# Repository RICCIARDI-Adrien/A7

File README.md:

# A7

A hand-made computer based on a 8-bit PIC18F26K22 microcontroller.

## Specifications

### CPU

* 64MHz PIC18 core (up to 16MIPS).
* 3896 RAM bytes.
* 32768 16-bit instruction words.

### Display

* 128x64 STN display with white pixels on blue backlight.
* 8-bit data interface with the microcontroller.

### Input

* Standard PS/2 keyboard support.
* Connect via standard PS/2 6-pin mini DIN connector.

### External storage

* On-board 128KB EEPROM (256-byte pages, 6ms maximum to write a page).
* Connected to a fast 4MHz SPI bus (less than 600us to read a full 256-byte page).

### Communication

* Standard RS-232 DB9 connector.
* Communication settings : 115200 bauds, no parity, one stop bit.

### Power supply

* Standard power supply jack.
* Input voltage from 7V to 24V with at least 200mA.
* Polarity reversal protection.

# Hardware

Schematics and PCB have been made with Eagle 7.5.  

# Software

Use Microchip XC8 compiler to build software.  
You have to add the following environment variable for the build system to find the compiler-provided include files :
```
XC8_INCLUDES_PATH
```
The variable content must be the full path to the XC8 include directory. Below is an example for a Windows machine (don't forget to add quotation marks if the path contains spaces) :
```
"C:\Program Files\Microchip\xc8\v1.42\include"
```
  
In order to download applications on the A7, you have to set the following environment variable with the serial port device used to communicate with the A7 (like /dev/ttyS0, /dev/ttyUSB0...) :
```
A7_APPLICATION_DOWNLOAD_SERIAL_PORT_DEVICE
```

# Casing

Casing panels have been drawn with LibreCAD.

# Photo gallery

## 128x64 pixels graphical display

## Casing assembly

## Other viewing angles

## Booted operating system

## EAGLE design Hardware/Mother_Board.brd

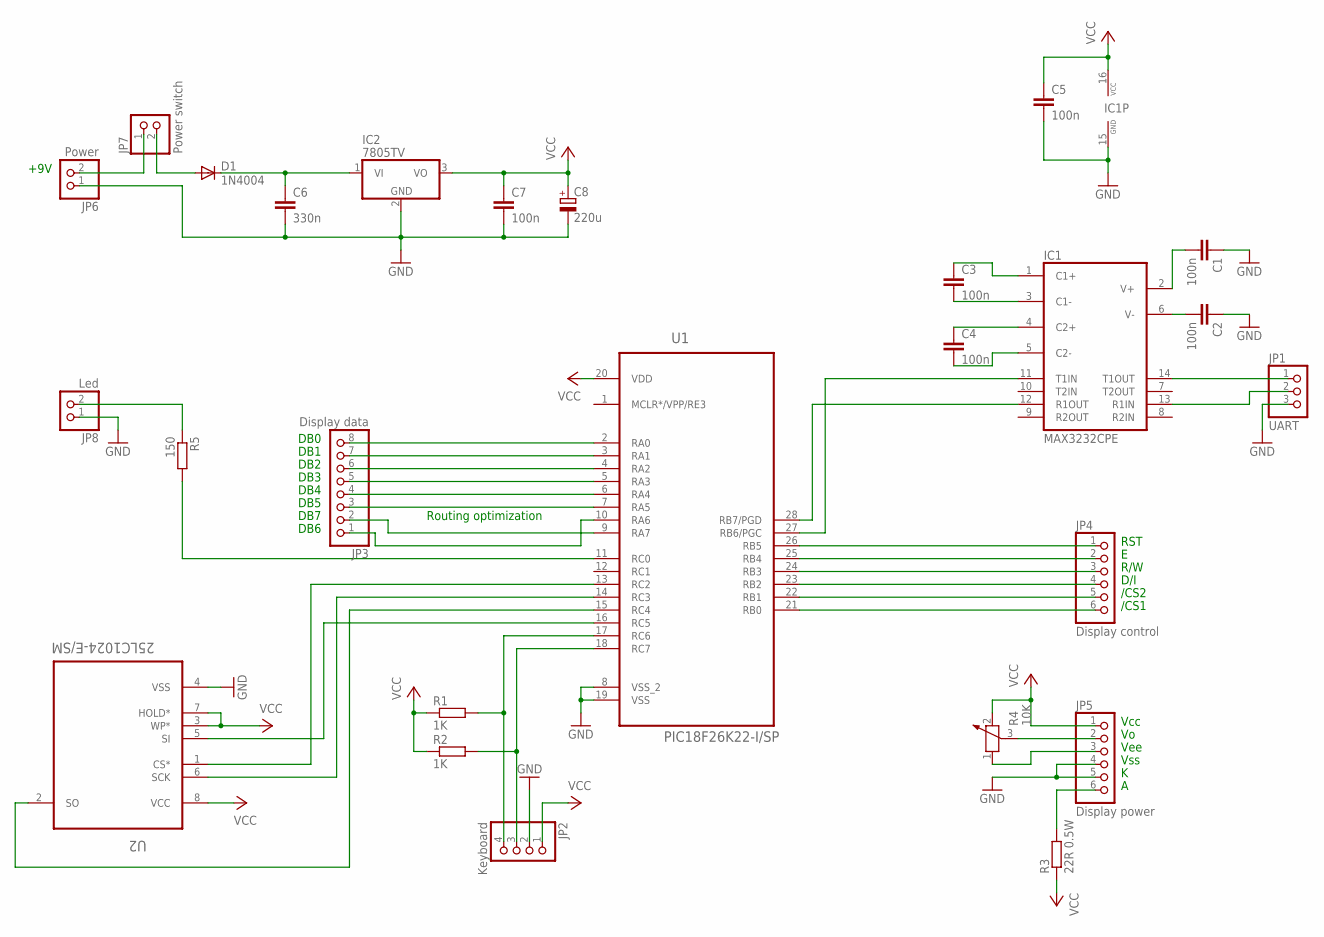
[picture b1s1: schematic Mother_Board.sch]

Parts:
C1, C2, C3, C4, C5, C7: 100n; C025-030X050
C6: 330n; C025-050X050
C8: 220u; B45181A
D1: 1N4004; DO41-10
IC1: MAX3232CPE; DIL16
IC2: 7805TV; TO220V
JP1: UART; 1X03
JP2: Keyboard; 1X04
JP3: Display data; 1X08
JP4: Display control; 1X06
JP5: Display power; 1X06
JP6: Power; 1X02
JP7: Power switch; 1X02
JP8: Led; 1X02
R1, R2: 1K; 0207/10
R3: 22R 0.5W; 0207/10
R4: 10K; PT-10S
R5: 150; 0207/10
U1: PIC18F26K22-I/SP; DIP254P762X508-28P
U2: 25LC1024-E/SM; SOIC127P794X203-8N

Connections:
GND: C1.1, C2.1, C5.2, C6.2, C7.2, C8.-, IC1.15 (GND), IC2.2 (GND), JP1.3, JP2.2, JP5.4, JP5.5, JP6.1, JP8.1, U1.8 (VSS_2), U1.19 (VSS), U2.4 (VSS)
unnamed: C3.1, IC1.1 (C1+)
unnamed: C3.2, IC1.3 (C1-)
unnamed: C4.1, IC1.4 (C2+)
unnamed: C4.2, IC1.5 (C2-)
unnamed: C1.2, IC1.2 (V+)
unnamed: IC1.12 (R1OUT), U1.28 (RB7/PGD)
unnamed: C2.2, IC1.6 (V-)
unnamed: IC1.11 (T1IN), U1.27 (RB6/PGC)
unnamed: IC1.14 (T1OUT), JP1.1
unnamed: IC1.13 (R1IN), JP1.2
unnamed: JP3.8, U1.2 (RA0)
unnamed: JP3.7, U1.3 (RA1)
unnamed: JP2.3, R2.2, U1.18 (RC7)
unnamed: JP2.4, R1.2, U1.17 (RC6)
unnamed: JP3.6, U1.4 (RA2)
unnamed: JP3.5, U1.5 (RA3)
unnamed: JP3.4, U1.6 (RA4)
unnamed: JP3.3, U1.7 (RA5)
unnamed: JP3.2, U1.9 (RA7)
unnamed: JP3.1, U1.10 (RA6)
unnamed: U1.16 (RC5), U2.5 (SI)
unnamed: U1.14 (RC3), U2.6 (SCK)
unnamed: U1.15 (RC4), U2.2 (SO)
unnamed: U1.13 (RC2), U2.1 (CS*)
unnamed: JP5.3, R4.1
unnamed: JP4.1, U1.26 (RB5)
unnamed: JP4.2, U1.25 (RB4)
unnamed: JP4.3, U1.24 (RB3)
unnamed: JP4.4, U1.23 (RB2)
unnamed: JP4.5, U1.22 (RB1)
unnamed: JP4.6, U1.21 (RB0)
unnamed: JP5.2, R4.3
unnamed: JP5.6, R3.2
unnamed: JP6.2, JP7.1
unnamed: D1.A, JP7.2
unnamed: C6.1, D1.C, IC2.1 (VI)
unnamed: R5.2, U1.11 (RC0)
unnamed: JP8.2, R5.1
VCC: C5.1, C7.1, C8.+, IC1.16 (VCC), IC2.3 (VO), JP2.1, JP5.1, R1.1, R2.1, R3.1, R4.2, U1.20 (VDD), U2.3 (WP*), U2.7 (HOLD*), U2.8 (VCC)

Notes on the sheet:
DB0
DB1
DB2
DB3
DB4
DB5
DB6
DB7
Vcc
Vee
Vss
/CS1
/CS2
D/I
R/W
RST
+9V
Routing optimization

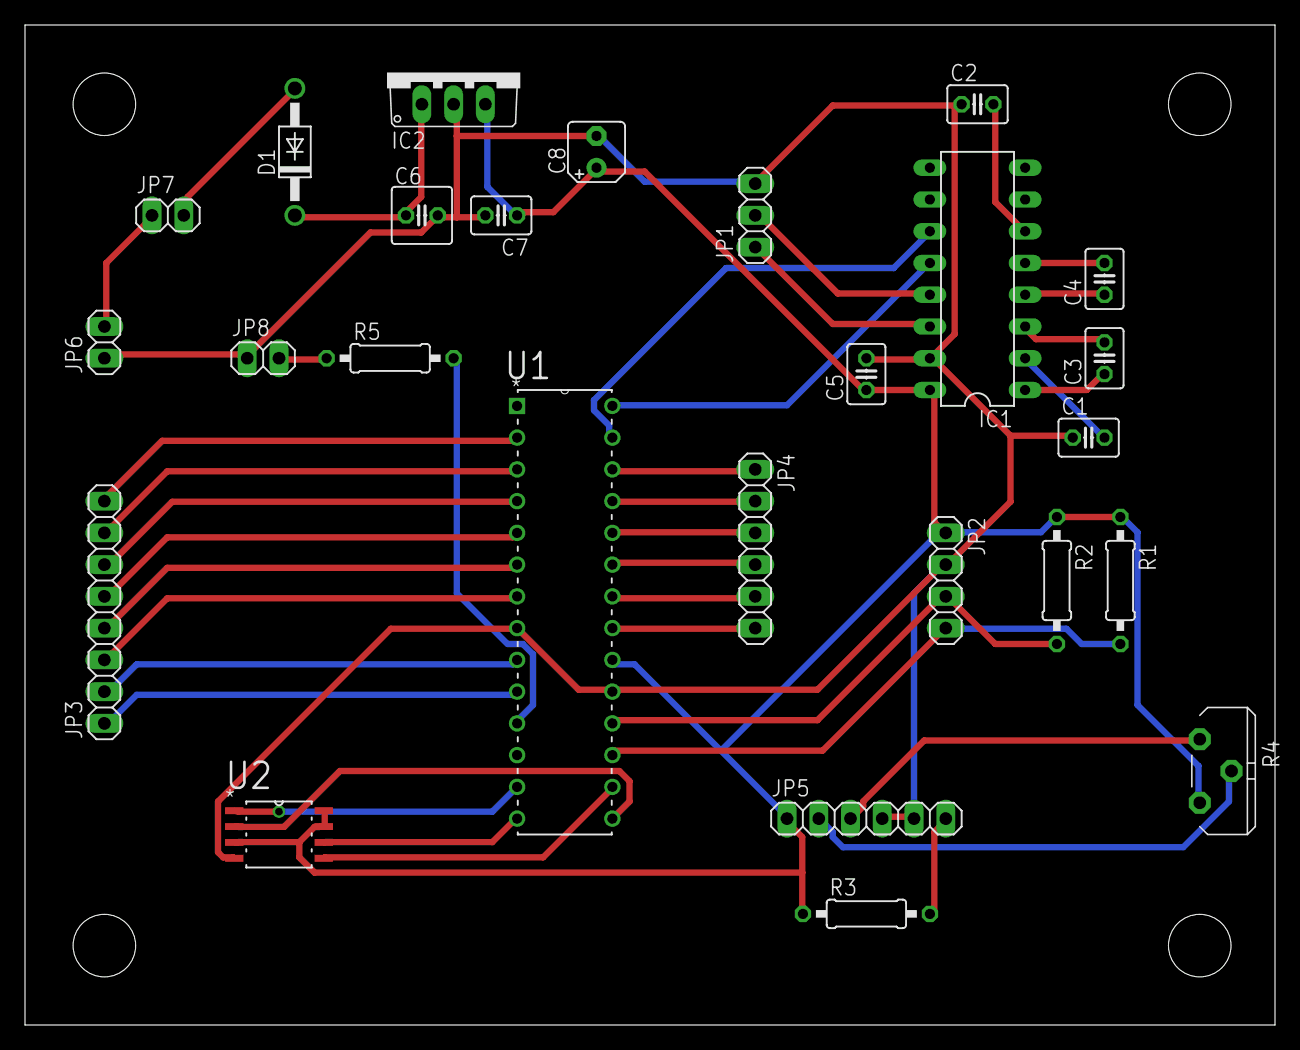
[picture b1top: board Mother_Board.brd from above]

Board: 2 copper layers, 100.0 x 80.0 mm, 26 parts (0 on the bottom side), 40 nets.

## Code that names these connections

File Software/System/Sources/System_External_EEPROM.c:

/** @file System_External_EEPROM.c
 * @see System_External_EEPROM.h for description.
 * @author Adrien RICCIARDI
 * @note Pins mapping : /SS = RC2, SCK = RC3, SDI = RC4, SDO = RC5.
 */
#include <System_External_EEPROM.h>
#include <xc.h>

//-------------------------------------------------------------------------------------------------
// Private constants and macros
//-------------------------------------------------------------------------------------------------
/** Read data chip command. */
#define SYSTEM_EXTERNAL_EEPROM_COMMAND_READ_DATA 0x03
/** Write data chip command. */
#define SYSTEM_EXTERNAL_EEPROM_COMMAND_WRITE_DATA 0x02
/** Read status register chip command. */
#define SYSTEM_EXTERNAL_EEPROM_COMMAND_READ_STATUS_REGISTER 0x05
/** Write enable chip command. */
#define SYSTEM_EXTERNAL_EEPROM_COMMAND_ENABLE_WRITE_OPERATION 0x06

/** Set chip /SS to low level (hold time must be at least 50ns, so loose a 62.5ns instruction to make sure /SS is held). */
#define SYSTEM_EXTERNAL_EEPROM_SELECT_DEVICE() \
{ \
	LATCbits.LATC2 = 0; \
	asm("nop"); \
}

/** Set chip /SS to high level (hold time must be at least 50ns, so loose a 62.5ns instruction to make sure /SS is held). */
#define SYSTEM_EXTERNAL_EEPROM_UNSELECT_DEVICE() \
{ \
	LATCbits.LATC2 = 1; \
	asm("nop"); \
}

//-------------------------------------------------------------------------------------------------
// Private functions
//-------------------------------------------------------------------------------------------------
/** Transfer a byte on the SPI bus.
 * @param Byte The byte to transmit.
 * @return The byte received from the addressed device.
 */
static unsigned char SystemExternalEEPROMTransferSPIByte(unsigned char Byte)
{
	// Start transfer
	SSP1BUF = Byte;
	
	// Wait for transfer end
	while (!PIR1bits.SSP1IF);
	PIR1bits.SSP1IF = 0; // Reset interrupt flag
	
	// Interrupt flag is set too soon (in the middle of the last clock pulse), so wait a full period (= 1/4MHz) to be sure transmission has finished
	asm("nop\n");
	asm("nop\n");
	asm("nop\n");
	asm("nop\n");
	
	// Get byte received from device
	return SSP1BUF;
}

//-------------------------------------------------------------------------------------------------
// Public functions
//-------------------------------------------------------------------------------------------------
void SystemExternalEEPROMInitialize(void)
{
	// Prepare pins to be used by the SPI module
	// Set all pins to digital
	ANSELC &= 0xC3;
	// Configure pins direction
	TRISCbits.TRISC2 = 0; // /SS pin
	TRISCbits.TRISC3 = 0; // SCK pin
	TRISCbits.TRISC4 = 1; // SDI pin
	TRISCbits.TRISC5 = 0; // SDO pin
	
	// Configure MSSP1 for SPI master operation
	SSP1STAT = 0; // Sample input data at middle of data output time, transmit on transition from idle to active clock state
	SSP1CON1 = 0x31; // Enable SPI module, use clock mode 1 to generate a rising edge when data is valid because EEPROM samples input data on clock rising edge, select SPI master mode with Fosc/16 = 4MHz clock (this is the fastest clock that seems to be working and stable)
	
	// Wake-up chip by doing a high-to-low transition on /CS pin (do twice to be sure it works)
	SYSTEM_EXTERNAL_EEPROM_UNSELECT_DEVICE();
	SYSTEM_EXTERNAL_EEPROM_SELECT_DEVICE();
	SYSTEM_EXTERNAL_EEPROM_UNSELECT_DEVICE();
	SYSTEM_EXTERNAL_EEPROM_SELECT_DEVICE();
}

void SystemExternalEEPROMReadPage(unsigned short Page_Number, unsigned char *Pointer_Buffer)
{
	unsigned short i;
	
	// Make sure address is in range
	if (Page_Number >= SYSTEM_EXTERNAL_EEPROM_PAGES_COUNT) return;
	
	SYSTEM_EXTERNAL_EEPROM_SELECT_DEVICE();
	// Send read command
	SystemExternalEEPROMTransferSPIByte(SYSTEM_EXTERNAL_EEPROM_COMMAND_READ_DATA);
	// Send 24-bit address
	SystemExternalEEPROMTransferSPIByte(Page_Number >> 8);
	SystemExternalEEPROMTransferSPIByte((unsigned char) Page_Number);
	SystemExternalEEPROMTransferSPIByte(0); // See SystemExternalEEPROMWritePage() for more details on address computation
	// Read a whole page
	for (i = 0; i < SYSTEM_EXTERNAL_EEPROM_PAGE_SIZE; i++)
	{
		*Pointer_Buffer = SystemExternalEEPROMTransferSPIByte(0);
		Pointer_Buffer++;
	}
	SYSTEM_EXTERNAL_EEPROM_UNSELECT_DEVICE();
}

void SystemExternalEEPROMWritePage(unsigned short Page_Number, unsigned char *Pointer_Buffer)
{
	unsigned short i;
	unsigned char Status_Register;
	
	// Make sure address is in range
	if (Page_Number >= SYSTEM_EXTERNAL_EEPROM_PAGES_COUNT) return;
	
	// Allow writing by setting the Write Enable Latch
	SYSTEM_EXTERNAL_EEPROM_SELECT_DEVICE();
	SystemExternalEEPROMTransferSPIByte(SYSTEM_EXTERNAL_EEPROM_COMMAND_ENABLE_WRITE_OPERATION);
	SYSTEM_EXTERNAL_EEPROM_UNSELECT_DEVICE(); // Device must be selected then unselected for the command to work, as specified by datasheet
	
	// Write data to specified page
	SYSTEM_EXTERNAL_EEPROM_SELECT_DEVICE();
	// Send write command
	SystemExternalEEPROMTransferSPIByte(SYSTEM_EXTERNAL_EEPROM_COMMAND_WRITE_DATA);
	// Send 24-bit address (as the parameter provided to the function is a 256-byte page address, there is only to multiply this value by 256 to get the byte address. This will lead to the 8 least significant bits set to zero. Below code avoids doing this useless computation and directly sends zero as the last address part)
	SystemExternalEEPROMTransferSPIByte(Page_Number >> 8);
	SystemExternalEEPROMTransferSPIByte((unsigned char) Page_Number);
	SystemExternalEEPROMTransferSPIByte(0);
	// Send data to write
	for (i = 0; i < SYSTEM_EXTERNAL_EEPROM_PAGE_SIZE; i++)
	{
		SystemExternalEEPROMTransferSPIByte(*Pointer_Buffer);
		Pointer_Buffer++;
	}
	SYSTEM_EXTERNAL_EEPROM_UNSELECT_DEVICE(); // Start write cycle
	
	// Wait for the write cycle to finish
	do
	{
		// Read status register
		SYSTEM_EXTERNAL_EEPROM_SELECT_DEVICE();
		SystemExternalEEPROMTransferSPIByte(SYSTEM_EXTERNAL_EEPROM_COMMAND_READ_STATUS_REGISTER); // Send command
		Status_Register = SystemExternalEEPROMTransferSPIByte(0); // Send a dummy byte to allow the device to transmit its answer
		SYSTEM_EXTERNAL_EEPROM_UNSELECT_DEVICE();
	} while (Status_Register & 0x01);
}

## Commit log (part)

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2017-04-23 Initial commit. Made a led blink.
2017-04-23 Started 'Find the number' application (used as a test application for now).
2017-04-24 Started system serial port module, transmission is working.
2017-04-24 Started system keyboard driver implementation. Keyboard raw scan codes are successfully received.
2017-04-25 Added AZERTY default key map to keyboard driver.
2017-04-25 Discarded by default keyboard extended code keys (but some keys can be explicitely kept).
2017-04-25 Added uppercase characters and left and right shift keys support.
2017-04-26 Started hardware mother board schematics : added RS-232 UART and PS/2 keyboard connection.
2017-05-01 Added LCD display module and SPI EEPROM to the schematics.
2017-05-01 Added led and power supply to the schematics.
2017-05-05 Added routed PCB.
2017-05-19 Started graphic LCD display driver implementation. Display can be successfully initialized.
2017-05-19 Added SystemDisplayClear() function to the display driver.
2017-05-20 Added SystemDisplayBeginRendering() and SystemDisplayEndRendering() functions to the display driver and a 'pong ball' test in the 'find the number' application.
2017-05-20 Added SystemDisplayRenderSprite() function to the display driver.
2017-05-20 Started Pong application to test the display functions on a real case.
2017-05-20 Unified Find The Number application makefile with Pong application one.
2017-05-22 Added system random functions.
2017-05-22 Added Benchmark application.
2017-05-22 Added system display frame timer functions.
2017-05-22 Used frame timer functions in the Benchmark application rendering loop to display whatever balls count with the same frame rate.
2017-05-29 Used a timer clocked by a non-stable oscillator to initialize the random numbers generator.
2017-05-29 Added LCD display letter sprites definition to resources.
2017-05-29 Added system display text rendering functions and uppercase letter sprites.
2017-05-30 Added system serial port SystemSerialPortReadByte() function.
2017-05-30 Reorganized display control signals to be in the same order than the display module pins.
2017-06-01 Used official TRIS registers bits names in keyboard and serial port drivers.
2017-06-01 Started system external EEPROM driver implementation, added SystemExternalEEPROMWritePage() function.
2017-06-02 Added A7 specifications to the README.
2017-06-03 Added sytem external EEPROM driver read page function and changed SPI clock polarity to make communication works.
2017-06-03 Fixed EEPROM SDI and SDO signals routing.
2017-06-07 Added casing panel DXF files.
2017-06-08 Added digit sprites to the display driver.
2017-06-08 Renamed 'begin' and 'end' display rendering functions with more generic names so they can be coherently used in applications other than games.
2017-06-08 Added casing panels picture to README.
2017-06-12 Renamed display font digits bitmap files with more coherent names.
2017-06-12 Added non-interrupt driven keyboard function needed by program manager application.
2017-06-14 Added system internal EEPROM driver.
2017-06-14 File system information can be loaded from the internal EEPROM in the Programs Manager application, and file names can be displayed.
2017-06-15 Added lowercase letter sprites to the system display driver.
2017-06-15 Used a constant to represent the escape key value in the system keyboard driver.
2017-06-15 Added a non-blocking function to the system serial port driver to tell whether a byte has been received.
2017-06-16 Fixed misaligned internal EEPROM read and write in the Programs Manager application, also added FileSystemStore() function.
2017-06-16 Added 'main' and 'download file' menus to Programs Manager application.
2017-06-16 Added 'A7 upload application' PC program.
2017-06-18 Put Programs Manager at the beginning of the program memory and relocated interrupts to jump into the application code. This is the safest way to allow to flash an application to the program memory w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
2017-06-18 Used Hex Parser git submodule in A7 Upload Application PC program.
2017-06-18 Used BINARY_NAME variable in System makefile as in other makefiles.
2017-06-18 Added microcontroller flash program memory driver to System.
2017-06-18 Made A7 Upload Application send application to the A7 directly starting from the relocated base address (it is useless to send the memory range reserved to the Programs Manager, and it loses a lot of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
2017-06-23 Simplified Programs Manager application downloading protocol.
2017-06-23 Fixed a bug in the Programs Manager download protocol.
2017-06-23 Fixed flash memory driver writing operation.
2017-06-23 Written the right file size value to the file system when downloading a file with the Programs Manager.
2017-06-23 Added the 'start program' feature to the Programs Manager.
2017-06-23 Added reception overflow handling to the serial port driver (this avoids to hang the UART if an overflow condition is detected).
2017-06-23 Added led support to System.
2017-06-23 Turned led on when Programs Manager is executing time consuming tasks.
2017-06-23 Moved microcontroller code into Microcontroller directory and added a common .mk file to gather some shared microcontroller applications variables.
2017-06-23 Routed led to RC0 instead of RE3 (which is input-only pin).
2017-06-24 Used applications rules .mk file in the Programs Manager makefile too.
2017-06-24 Added 'delete file' menu to the Programs Manager.
2017-06-24 Displayed exit message at the Programs Manager file selection menus bottom.
2017-06-24 Made Display system driver display a rectangle to indicate an unknown character.
2017-06-24 Added punctuation character sprites to the display driver.
2017-06-26 Added new line character support and screen scrolling when the text cursor reached the screen bottom to the display driver.
2017-06-26 Prevented control characters from being displayed in the display driver.
2017-06-26 Execute the screen scrolling code after the character has been displayed to avoid handling corner cases when a control character is typed at the end of a line.
2017-06-26 Added backspace support to display driver text mode. Sprites XOR rendering has been replaced by 'overwrite' rendering mode to make it work.
2017-06-26 Added XC8 includes path to the applications rules.
2017-06-30 Implemented the real Find The Number game.
2017-06-30 Fixed bad register name in system serial port driver.
2017-06-30 Added SystemExitProgram() function.
2017-06-30 Ignored A7 Upload Application binary on Linux too.
2017-07-09 Added a main makefile in the Microcontroller directory with automatic applications detection and rules autocompletion.
2017-07-09 Moved Applications_Rules.mk rules into the main makefile.
2017-07-09 Added download rule to main makefile.
2017-07-09 Made special rules for Programs Manager as it is not a regular application.
2017-07-09 Renamed APPLICATIONS_RULES_xxx constants in MAIN_MAKEFILE_xxx constants for more coherency.
2017-07-09 Fixed Programs Manager keyboard hanging bug.
2017-07-14 Added 'game' keys (arrows and space bar for now) support to the system keyboard driver.
2017-07-16 Restored XORing in the display rendering sprite function to allow multiple sprites with a height smaller than 8 pixels to be drawn on the same display byte without overwritting the whole byte.
2017-07-16 Added a system function to tell in a non-blocking way whether a keyboard key is available to read.
2017-07-16 Allowed rendering of sprites with a height less than 8 pixels now that XOR rendering is enabled.
2017-07-18 Fixed a typo in a comment.
2017-07-18 Improved applications and Programs Manager initializations (interrupts are no more enabled on the Programs Manager and clock is no more reconfigured on application start). Programs Manager seems to h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
2017-07-18 Added Game of Life application.
2017-07-19 Added stuck world and 1-period oscillators detection to the Game of Life application.
2017-07-19 Added a key to toggle 'fast mode' in the Game of Life application.
2017-07-19 Added 3-period oscillators detection to the Game of Life application.
2017-10-22 Started AES Test application implementation. Added S-Box content and SubBytes() step.
2017-10-22 Added ShiftRows() step to the AES Test application.
2017-10-22 Improved AESStepShiftRows() function readability in AES Test application.
2017-10-22 Added MixColumns() step to AES Test application.
2017-10-22 Added key schedule word rotation and substitution functions to AES Test application.
2017-10-22 Added key expansion step to AES Test application.
2017-10-24 Added AddRoundKey() step to AES Test application.
2017-10-25 Started AES cipher algorithm implementation in AES Test application.
2017-10-25 Fixed AES substitution box and MixColumns() step in AES Test application.
2017-10-26 AES-256 cipher algorithm is working in AES Test application.
2017-10-29 Added AES CBC support to AES Test application.
2017-10-29 Randomized initial AES CBC block in AES Test application.
2017-10-29 Fixed AES Test application warning due to AESStepSubstituteBytes().
2017-10-29 Used system led to show working activity in the AES Test application.
2017-10-29 Made a little speed improvement in the AES Test application.
2017-11-04 Automatically create the Objects directory when building an application.
2017-11-04 Standardized application directories so paths can be provided by the main makefile to avoid duplicating paths definition in all applications.
2017-11-04 Handled --objdir and --outdir compiler options in the main makefile.
2017-11-04 Also handled application local include directory directly from the main makefile.
2017-11-04 Automatically remove objects directory when executing an application 'clean' makefile rule.
2017-11-15 Fixed a bug in the SystemDisplayRenderTextCharacter() function : '\b' character was not erasing the text at the good location.
2018-01-03 Used a better pseudo-random numbers generator in System library.
2018-01-23 Started Space Avoiders application. Added classic Space Invaders game alien sprites.
2018-01-23 Forced quotes around A7 application name into program downloading makefile rule to avoid adding quotes to each 'Application_Name_On_A7.txt' file.
2018-04-07 Fixed a type conversion warning in Programs Manager.
2018-04-27 Moved bouncing balls benchmark to a dedicated file in Benchmark application.
2018-04-27 Added a main menu to Benchmark application.
2018-04-27 Added floating point arithmetic benchmark to Benchmark application.
2018-04-28 Improved floating point arithmetic precision in Benchmark application.
2018-04-28 Removed automatic microcontroller application build when calling 'make <application>-download' rule.
2018-04-28 Fixed Doxygen tags typo in System_Random.h header.
2018-04-28 Added random numbers generator benchmark to Benchmark application.
2018-04-28 Improved system display API to make its use more intuitive.
2018-04-28 Added a colored message shown when compiling a microcontroller application to make full build easier to understand.
2018-04-28 Simplified microcontroller software makefile by removing Programs Manager specific makefile rules.
2018-04-28 Fixed microcontroller software makefile default rules that were rebuilding everything on each call.
2019-10-19 Removed now useless XC8 include path from build system.
2019-10-19 Fixed a build system trick that prevented system library to be built using XC8 2.05 and newer.
2019-10-19 Ignored ELF files created by XC8 2.10.
2019-10-19 Improved application name on target specification.
2019-10-20 Improved applications build by triggering a rebuild if a source file has been modified.
2019-10-20 Added SystemDisplaySetPixelState() system library function.
2019-10-20 Started Demo application. Demos are heavily inspired from Text Games System ones.
2019-10-20 Used function pointers to easily handle as many demos as needed.
2019-10-20 Added 'fill screen from bottom to top' demo.
2019-10-20 Added 'fill screen from left to right' demo.
2019-10-20 Added 'fill screen from right to left' demo.
2019-10-20 Added 'fill screen with square pattern' demo.
2019-10-20 Added 'falling snow' demo.
2020-04-24 Added project pictures to README.md.
2020-04-24 Fixed README.md picture URLs.
